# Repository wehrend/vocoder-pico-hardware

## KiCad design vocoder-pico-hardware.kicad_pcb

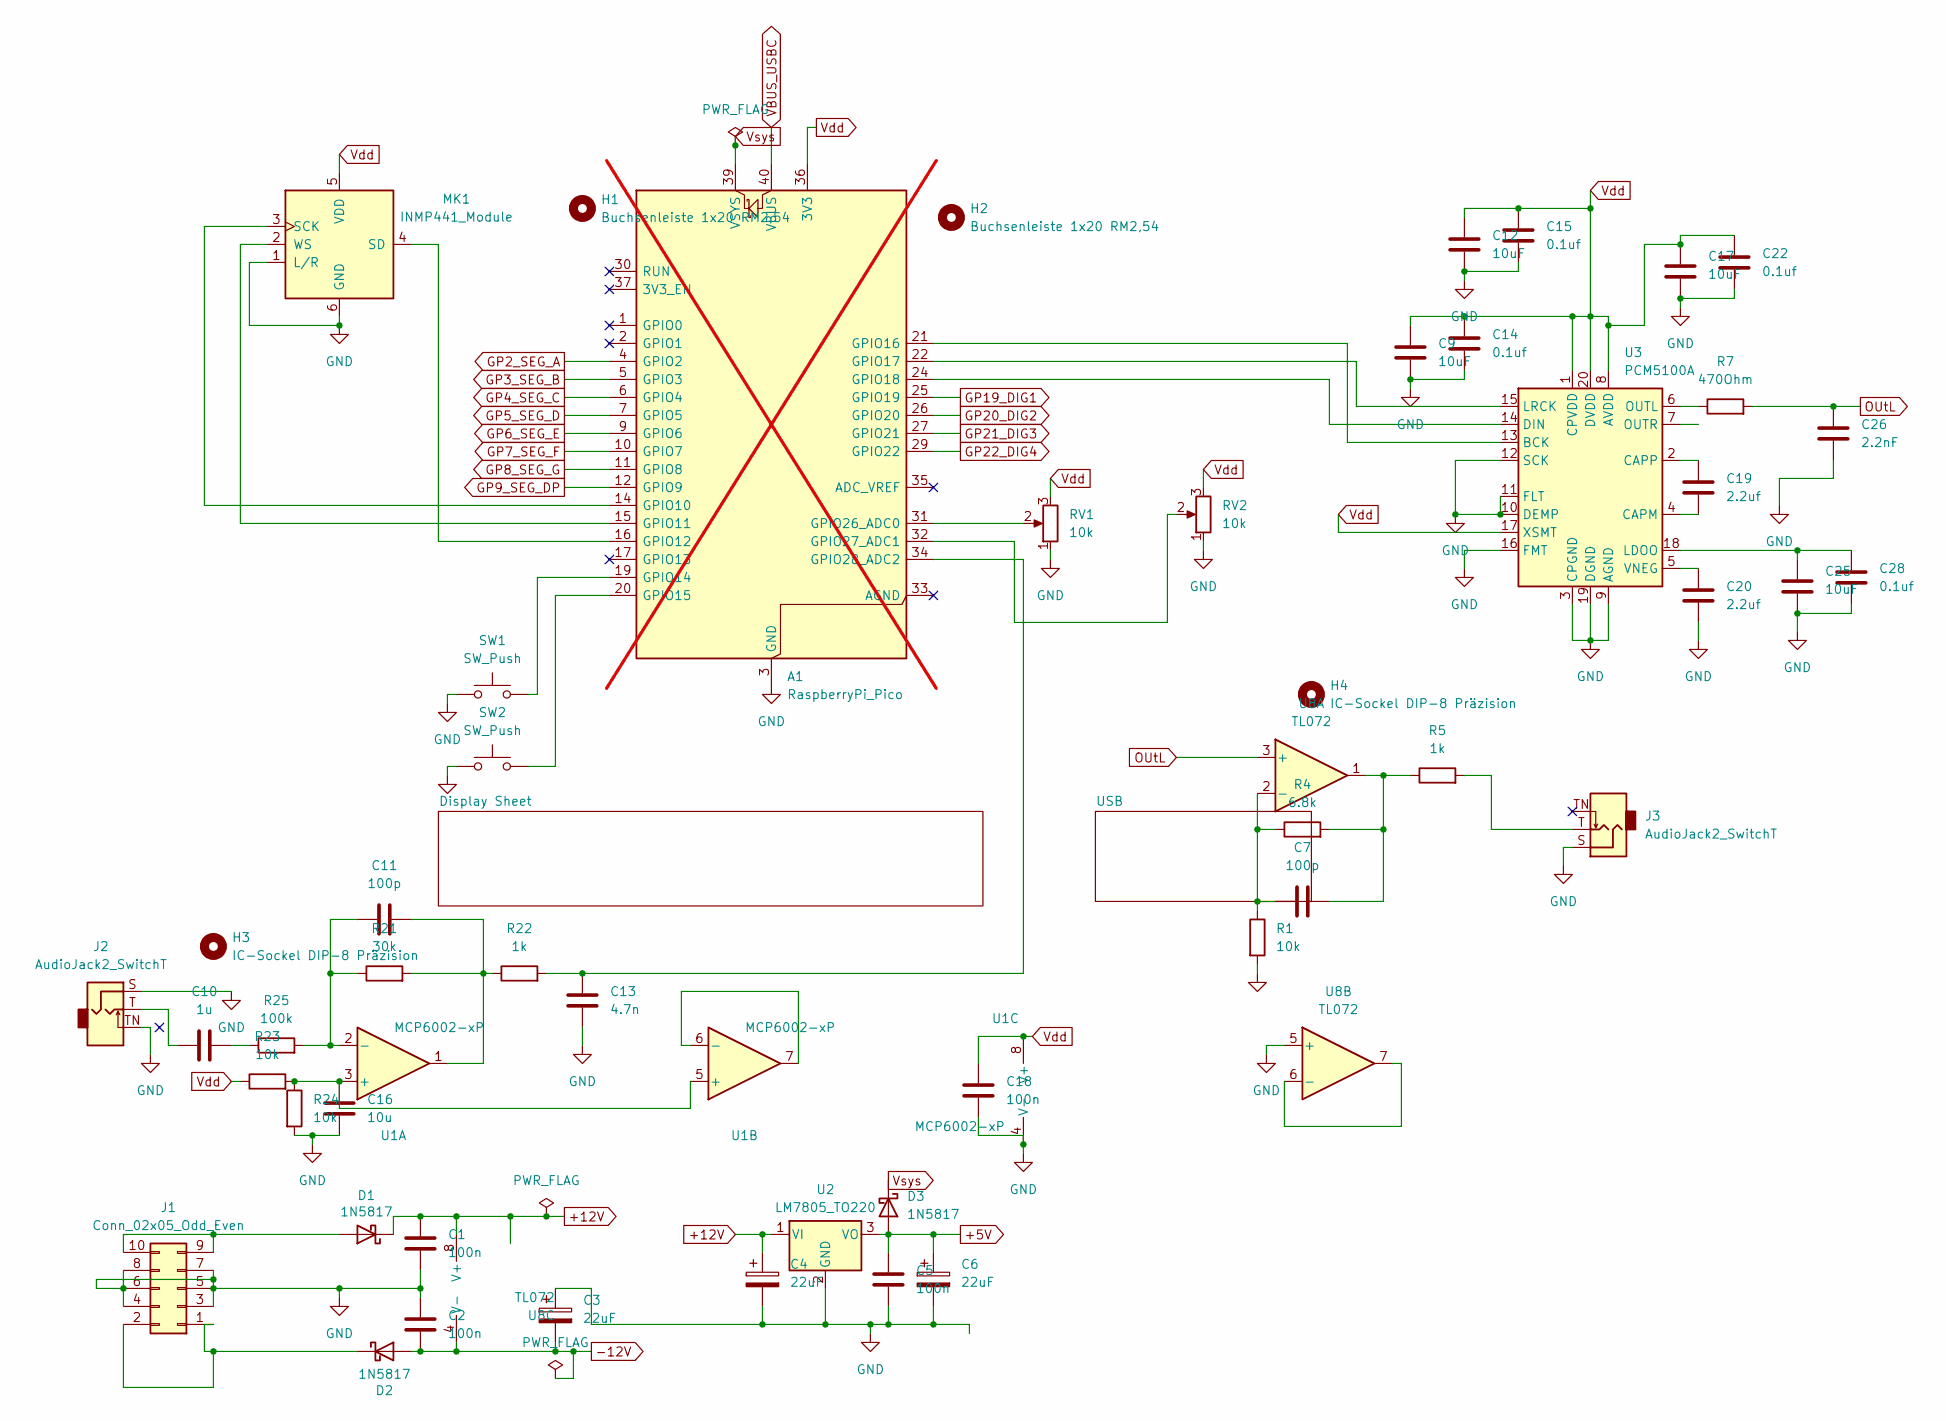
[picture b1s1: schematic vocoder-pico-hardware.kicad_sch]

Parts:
A1: RaspberryPi_Pico; RaspberryPi_Pico_Common_Unspecified; not fitted
C1, C2, C5, C18: 100n; C_Disc_D5.0mm_W2.5mm_P5.00mm
C3, C4, C6: 22uF; CP_Radial_D5.0mm_P2.00mm
C7, C11: 100p; C_Disc_D5.0mm_W2.5mm_P5.00mm
C9, C12, C17, C25: 10uF; C_0805_2012Metric
C10: 1u; C_Disc_D5.0mm_W2.5mm_P5.00mm
C13: 4.7n; C_Disc_D5.0mm_W2.5mm_P5.00mm
C14, C15, C22, C28: 0.1uf; C_0805_2012Metric
C16: 10u; C_Disc_D5.0mm_W2.5mm_P5.00mm
C19, C20: 2.2uf; C_0805_2012Metric
C26: 2.2nF; C_0805_2012Metric
D1, D2, D3: 1N5817; D_DO-41_SOD81_P10.16mm_Horizontal
H1, H2: Buchsenleiste 1x20 RM2,54
H3, H4: IC-Sockel DIP-8 Präzision
J1: Conn_02x05_Odd_Even; IDC-Header_2x05_P2.54mm_Vertical
J2, J3: AudioJack2_SwitchT; Jack_3.5mm_QingPu_WQP-PJ398SM_Vertical_CircularHoles
MK1: INMP441_Module; INMP441_Module_Socket
R1, R23, R24: 10k; R_0805_2012Metric
R4: 6.8k; R_0805_2012Metric
R5: 1k; R_Axial_DIN0207_L6.3mm_D2.5mm_P7.62mm_Horizontal
R7: 470Ohm; R_0805_2012Metric
R21: 30k; R_0805_2012Metric
R22: 1k; R_0805_2012Metric
R25: 100k; R_0805_2012Metric
RV1, RV2: 10k; Potentiometer_Alpha_RD901F-40-00D_Single_Vertical
SW1, SW2: SW_Push; SW_PUSH_6mm
U1: MCP6002-xP; DIP-8_W7.62mm_Socket
U2: LM7805_TO220; TO-220-3_Vertical
U3: PCM5100A; TSSOP-20_4.4x6.5mm_P0.65mm
U8: TL072; DIP-8_W7.62mm_Socket

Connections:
+5V: C5.1, C6.1, D3.2 (A), U2.3 (VO)
+12V: C1.1, C4.1, D1.1 (K), U2.1 (VI), U8.8 (V+)
-12V: C2.2, C3.2, D2.2 (A), U8.4 (V-)
GND: A1.3 (GND), A1.8 (GND), A1.13 (GND), A1.18 (GND), A1.23 (GND), A1.28 (GND), A1.38 (GND), C1.2, C2.1, C3.1, C4.2, C5.2, C6.2, C9.2, C12.2, C13.2, C14.2, C15.2, C16.2, C17.2, C18.2, C20.2, C22.2, C25.2, C26.2, C28.2, J1.3, J1.4, J1.5, J1.6, J1.7, J1.8, J2.S, J2.TN, J3.S, MK1.1 (L/R), MK1.6 (GND), R1.2, R24.2, RV1.1, RV2.1, SW1.1, SW2.1, U1.4 (V-), U2.2 (GND), U3.3 (CPGND), U3.9 (AGND), U3.10 (DEMP), U3.11 (FLT), U3.12 (SCK), U3.16 (FMT), U3.19 (DGND), U8.5 (+); also elsewhere on the board
GP2_SEG_A: A1.4 (GPIO2); also elsewhere on the board
GP3_SEG_B: A1.5 (GPIO3); also elsewhere on the board
GP4_SEG_C: A1.6 (GPIO4); also elsewhere on the board
GP5_SEG_D: A1.7 (GPIO5); also elsewhere on the board
GP6_SEG_E: A1.9 (GPIO6); also elsewhere on the board
GP7_SEG_F: A1.10 (GPIO7); also elsewhere on the board
GP8_SEG_G: A1.11 (GPIO8); also elsewhere on the board
GP9_SEG_DP: A1.12 (GPIO9); also elsewhere on the board
GP19_DIG1: A1.25 (GPIO19); also elsewhere on the board
GP20_DIG2: A1.26 (GPIO20); also elsewhere on the board
GP21_DIG3: A1.27 (GPIO21); also elsewhere on the board
GP22_DIG4: A1.29 (GPIO22); also elsewhere on the board
unnamed: A1.14 (GPIO10), MK1.3 (SCK)
unnamed: A1.15 (GPIO11), MK1.2 (WS)
unnamed: A1.16 (GPIO12), MK1.4 (SD)
unnamed: A1.19 (GPIO14), SW1.2
unnamed: A1.20 (GPIO15), SW2.2
unnamed: A1.21 (GPIO16), U3.13 (BCK)
unnamed: A1.22 (GPIO17), U3.15 (LRCK)
unnamed: A1.24 (GPIO18), U3.14 (DIN)
unnamed: A1.31 (GPIO26_ADC0), RV1.2
unnamed: A1.32 (GPIO27_ADC1), RV2.2
unnamed: A1.34 (GPIO28_ADC2), C13.1, R22.2
unnamed: C7.2, R4.2, R5.1, U8.1
unnamed: C10.1, J2.T
unnamed: C10.2, R25.1
unnamed: C11.2, R21.2, R22.1, U1.1
unnamed: D1.2 (A), J1.9, J1.10
unnamed: D2.1 (K), J1.1, J1.2
unnamed: J3.T, R5.2
unnamed: C16.1, R23.2, R24.1, U1.3 (+), U1.5 (+)
unnamed: C11.1, R21.1, R25.2, U1.2 (-)
unnamed: U1.6 (-), U1.7
unnamed: C19.2, U3.4 (CAPM)
unnamed: C19.1, U3.2 (CAPP)
unnamed: C25.1, C28.1, U3.18 (LDOO)
unnamed: R7.1, U3.6 (OUTL)
unnamed: C20.1, U3.5 (VNEG)
unnamed: C7.1, R1.1, R4.1, U8.2 (-)
unnamed: U8.6 (-), U8.7
OUtL: C26.1, R7.2, U8.3 (+)
VBUS_USBC: A1.40 (VBUS); also elsewhere on the board
Vdd: A1.36 (3V3), C9.1, C12.1, C14.1, C15.1, C17.1, C18.1, C22.1, MK1.5 (VDD), R23.1, RV1.3, RV2.3, U1.8 (V+), U3.1 (CPVDD), U3.8 (AVDD), U3.17 (XSMT), U3.20 (DVDD)
Vsys: A1.39 (VSYS), D3.1 (K)

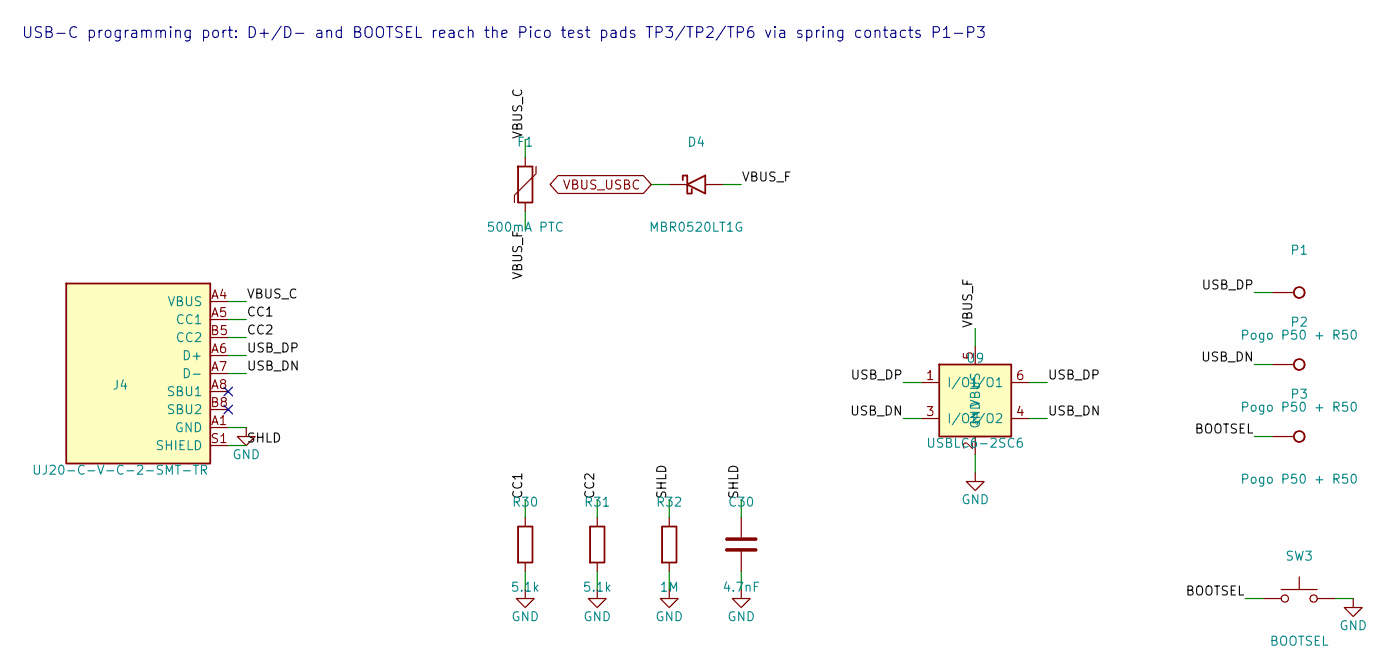
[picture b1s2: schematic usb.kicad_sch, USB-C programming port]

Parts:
C30: 4.7nF; C_0805_2012Metric
D4: MBR0520LT1G; D_SOD-123
F1: 500mA PTC; R_0805_2012Metric
J4: UJ20-C-V-C-2-SMT-TR; USB_C_SameSky_UJ20-C-V-C-2_Vertical; MPN UJ20-C-V-C-2-SMT-TR
P1, P2, P3: Pogo P50 + R50; Pogo_P50_R50
R30, R31: 5.1k; R_0805_2012Metric
R32: 1M; R_0805_2012Metric
SW3: BOOTSEL; SW_PUSH_6mm
U9: USBLC6-2SC6; SOT-23-6

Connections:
/USB/BOOTSEL: P3.1, SW3.1
/USB/CC1: J4.A5 (CC1), R30.1
/USB/CC2: J4.B5 (CC2), R31.1
/USB/SHLD: C30.1, J4.S1 (SHIELD), R32.1
/USB/USB_DN: J4.A7 (D-), J4.B7 (D-), P2.1, U9.3 (I/O2), U9.4 (I/O2)
/USB/USB_DP: J4.A6 (D+), J4.B6 (D+), P1.1, U9.1 (I/O1), U9.6 (I/O1)
/USB/VBUS_C: F1.1, J4.A4 (VBUS), J4.A9 (VBUS), J4.B4 (VBUS), J4.B9 (VBUS)
/USB/VBUS_F: D4.2 (A), F1.2, U9.5 (VBUS)
GND: C30.2, J4.A1 (GND), J4.A12 (GND), J4.B1 (GND), J4.B12 (GND), R30.2, R31.2, R32.2, SW3.2, U9.2 (GND); also elsewhere on the board
VBUS_USBC: D4.1 (K); also elsewhere on the board

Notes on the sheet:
USB-C programming port: D+/D- and BOOTSEL reach the Pico test pads TP3/TP2/TP6 via spring contacts P1-P3

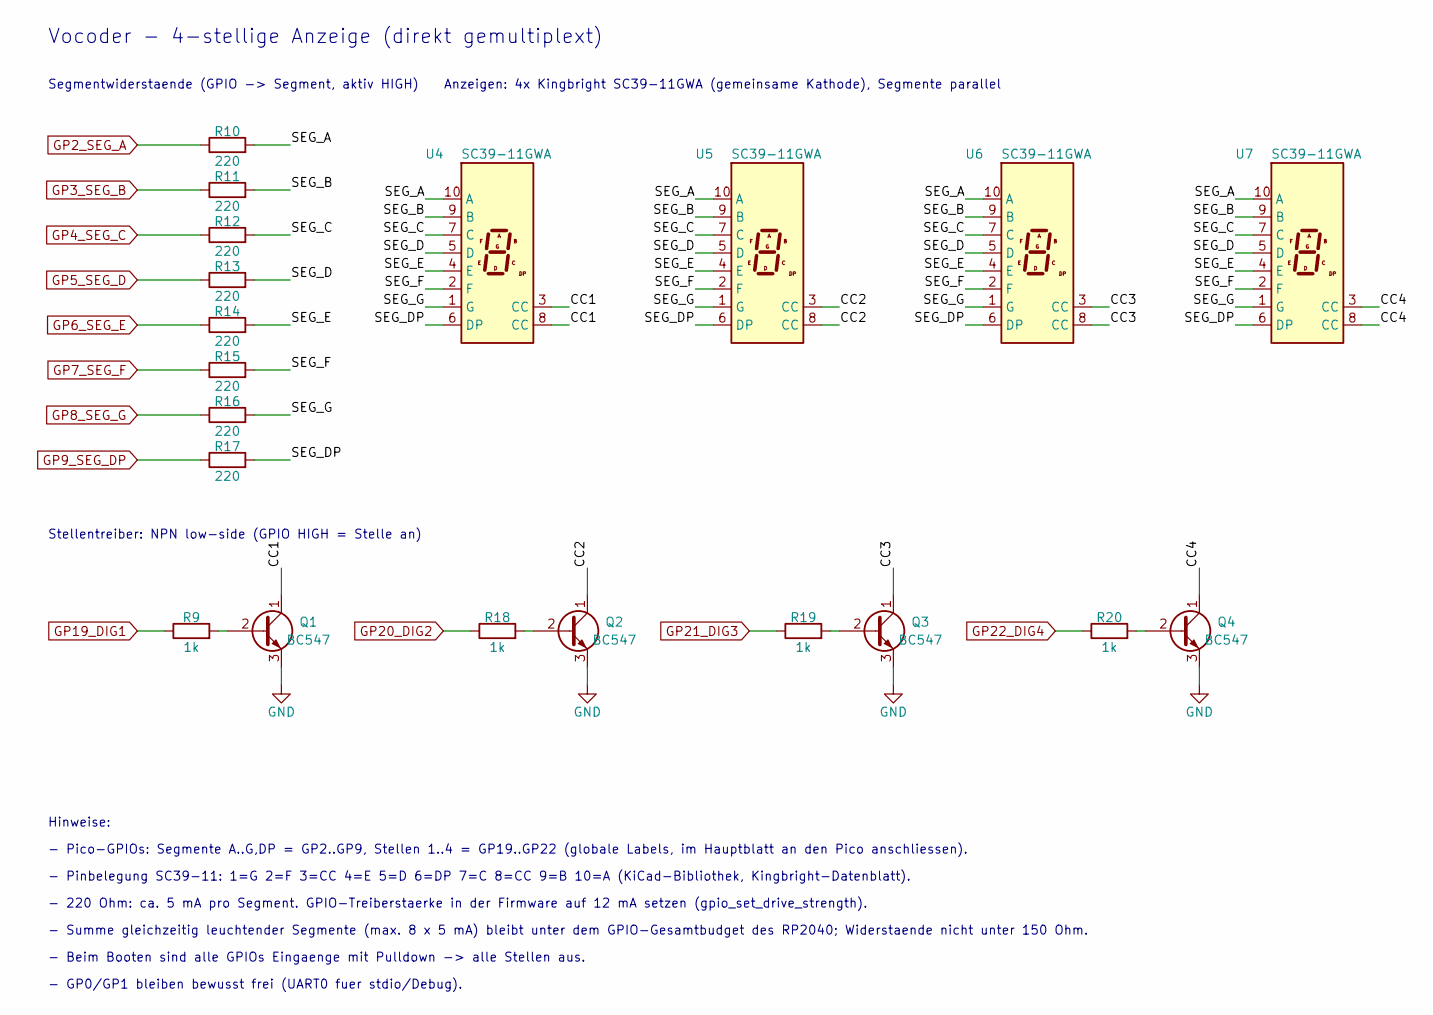
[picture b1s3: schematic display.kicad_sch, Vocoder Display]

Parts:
Q1, Q2, Q3, Q4: BC547; TO-92_Inline
R9, R18, R19, R20: 1k; R_Axial_DIN0207_L6.3mm_D2.5mm_P7.62mm_Horizontal
R10, R11, R12, R13, R14, R15, R16, R17: 220; R_Axial_DIN0207_L6.3mm_D2.5mm_P7.62mm_Horizontal
U4, U5, U6, U7: SC39-11GWA; Sx39-1xxxxx

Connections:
/Display Sheet/CC1: Q1.1 (C), U4.3 (CC), U4.8 (CC)
/Display Sheet/CC2: Q2.1 (C), U5.3 (CC), U5.8 (CC)
/Display Sheet/CC3: Q3.1 (C), U6.3 (CC), U6.8 (CC)
/Display Sheet/CC4: Q4.1 (C), U7.3 (CC), U7.8 (CC)
/Display Sheet/SEG_A: R10.2, U4.10 (A), U5.10 (A), U6.10 (A), U7.10 (A)
/Display Sheet/SEG_B: R11.2, U4.9 (B), U5.9 (B), U6.9 (B), U7.9 (B)
/Display Sheet/SEG_C: R12.2, U4.7 (C), U5.7 (C), U6.7 (C), U7.7 (C)
/Display Sheet/SEG_D: R13.2, U4.5 (D), U5.5 (D), U6.5 (D), U7.5 (D)
/Display Sheet/SEG_DP: R17.2, U4.6 (DP), U5.6 (DP), U6.6 (DP), U7.6 (DP)
/Display Sheet/SEG_E: R14.2, U4.4 (E), U5.4 (E), U6.4 (E), U7.4 (E)
/Display Sheet/SEG_F: R15.2, U4.2 (F), U5.2 (F), U6.2 (F), U7.2 (F)
/Display Sheet/SEG_G: R16.2, U4.1 (G), U5.1 (G), U6.1 (G), U7.1 (G)
GND: Q1.3 (E), Q2.3 (E), Q3.3 (E), Q4.3 (E); also elsewhere on the board
GP2_SEG_A: R10.1; also elsewhere on the board
GP3_SEG_B: R11.1; also elsewhere on the board
GP4_SEG_C: R12.1; also elsewhere on the board
GP5_SEG_D: R13.1; also elsewhere on the board
GP6_SEG_E: R14.1; also elsewhere on the board
GP7_SEG_F: R15.1; also elsewhere on the board
GP8_SEG_G: R16.1; also elsewhere on the board
GP9_SEG_DP: R17.1; also elsewhere on the board
GP19_DIG1: R9.1; also elsewhere on the board
GP20_DIG2: R18.1; also elsewhere on the board
GP21_DIG3: R19.1; also elsewhere on the board
GP22_DIG4: R20.1; also elsewhere on the board
unnamed: Q1.2 (B), R9.2
unnamed: Q2.2 (B), R18.2
unnamed: Q3.2 (B), R19.2
unnamed: Q4.2 (B), R20.2

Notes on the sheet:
- Beim Booten sind alle GPIOs Eingaenge mit Pulldown -> alle Stellen aus.
- Pinbelegung SC39-11: 1=G 2=F 3=CC 4=E 5=D 6=DP 7=C 8=CC 9=B 10=A (KiCad-Bibliothek, Kingbright-Datenblatt).
Stellentreiber: NPN low-side (GPIO HIGH = Stelle an)
- Summe gleichzeitig leuchtender Segmente (max. 8 x 5 mA) bleibt unter dem GPIO-Gesamtbudget des RP2040; Widerstaende nicht unter 150 Ohm.
- 220 Ohm: ca. 5 mA pro Segment. GPIO-Treiberstaerke in der Firmware auf 12 mA setzen (gpio_set_drive_strength).
- Pico-GPIOs: Segmente A..G,DP = GP2..GP9, Stellen 1..4 = GP19..GP22 (globale Labels, im Hauptblatt an den Pico anschliessen).
Segmentwiderstaende (GPIO -> Segment, aktiv HIGH)
Vocoder - 4-stellige Anzeige (direkt gemultiplext)
- GP0/GP1 bleiben bewusst frei (UART0 fuer stdio/Debug).
Anzeigen: 4x Kingbright SC39-11GWA (gemeinsame Kathode), Segmente parallel
Hinweise:

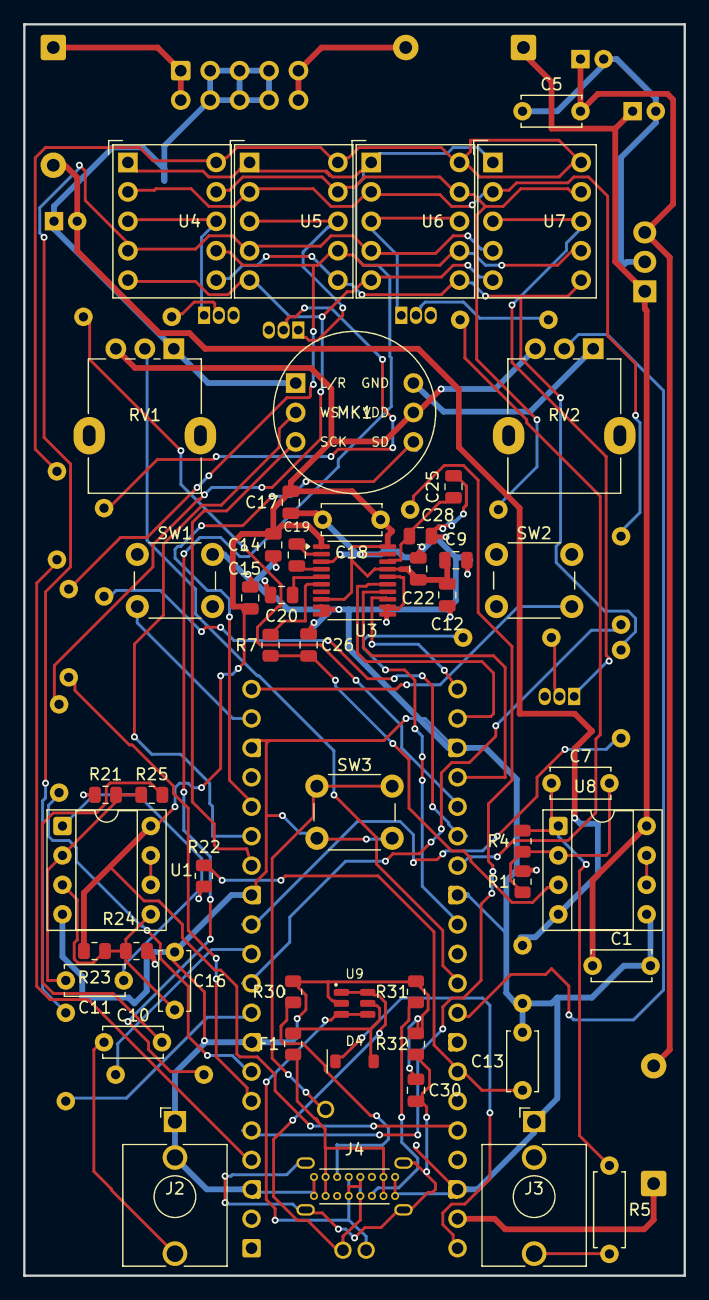
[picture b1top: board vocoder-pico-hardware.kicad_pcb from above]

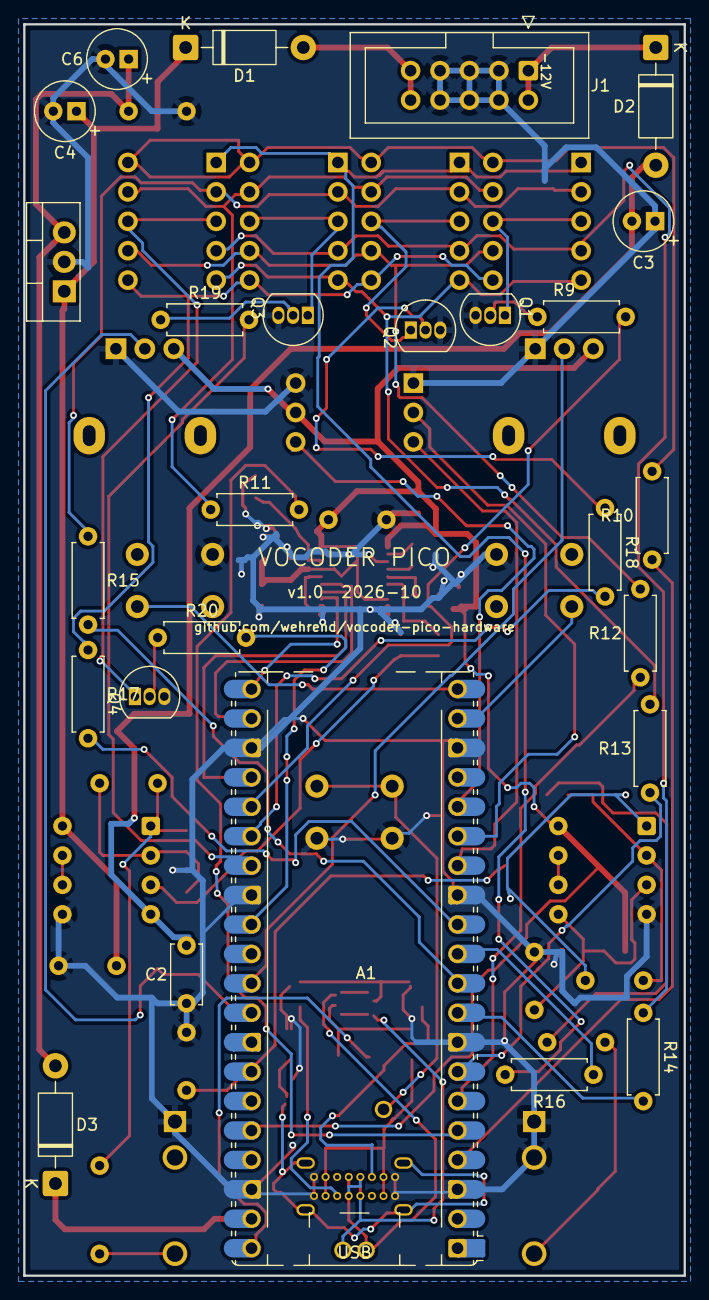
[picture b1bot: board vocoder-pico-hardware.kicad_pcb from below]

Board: 2 copper layers, 57.0 x 108.0 mm, 80 parts (29 on the bottom side), 72 nets.
